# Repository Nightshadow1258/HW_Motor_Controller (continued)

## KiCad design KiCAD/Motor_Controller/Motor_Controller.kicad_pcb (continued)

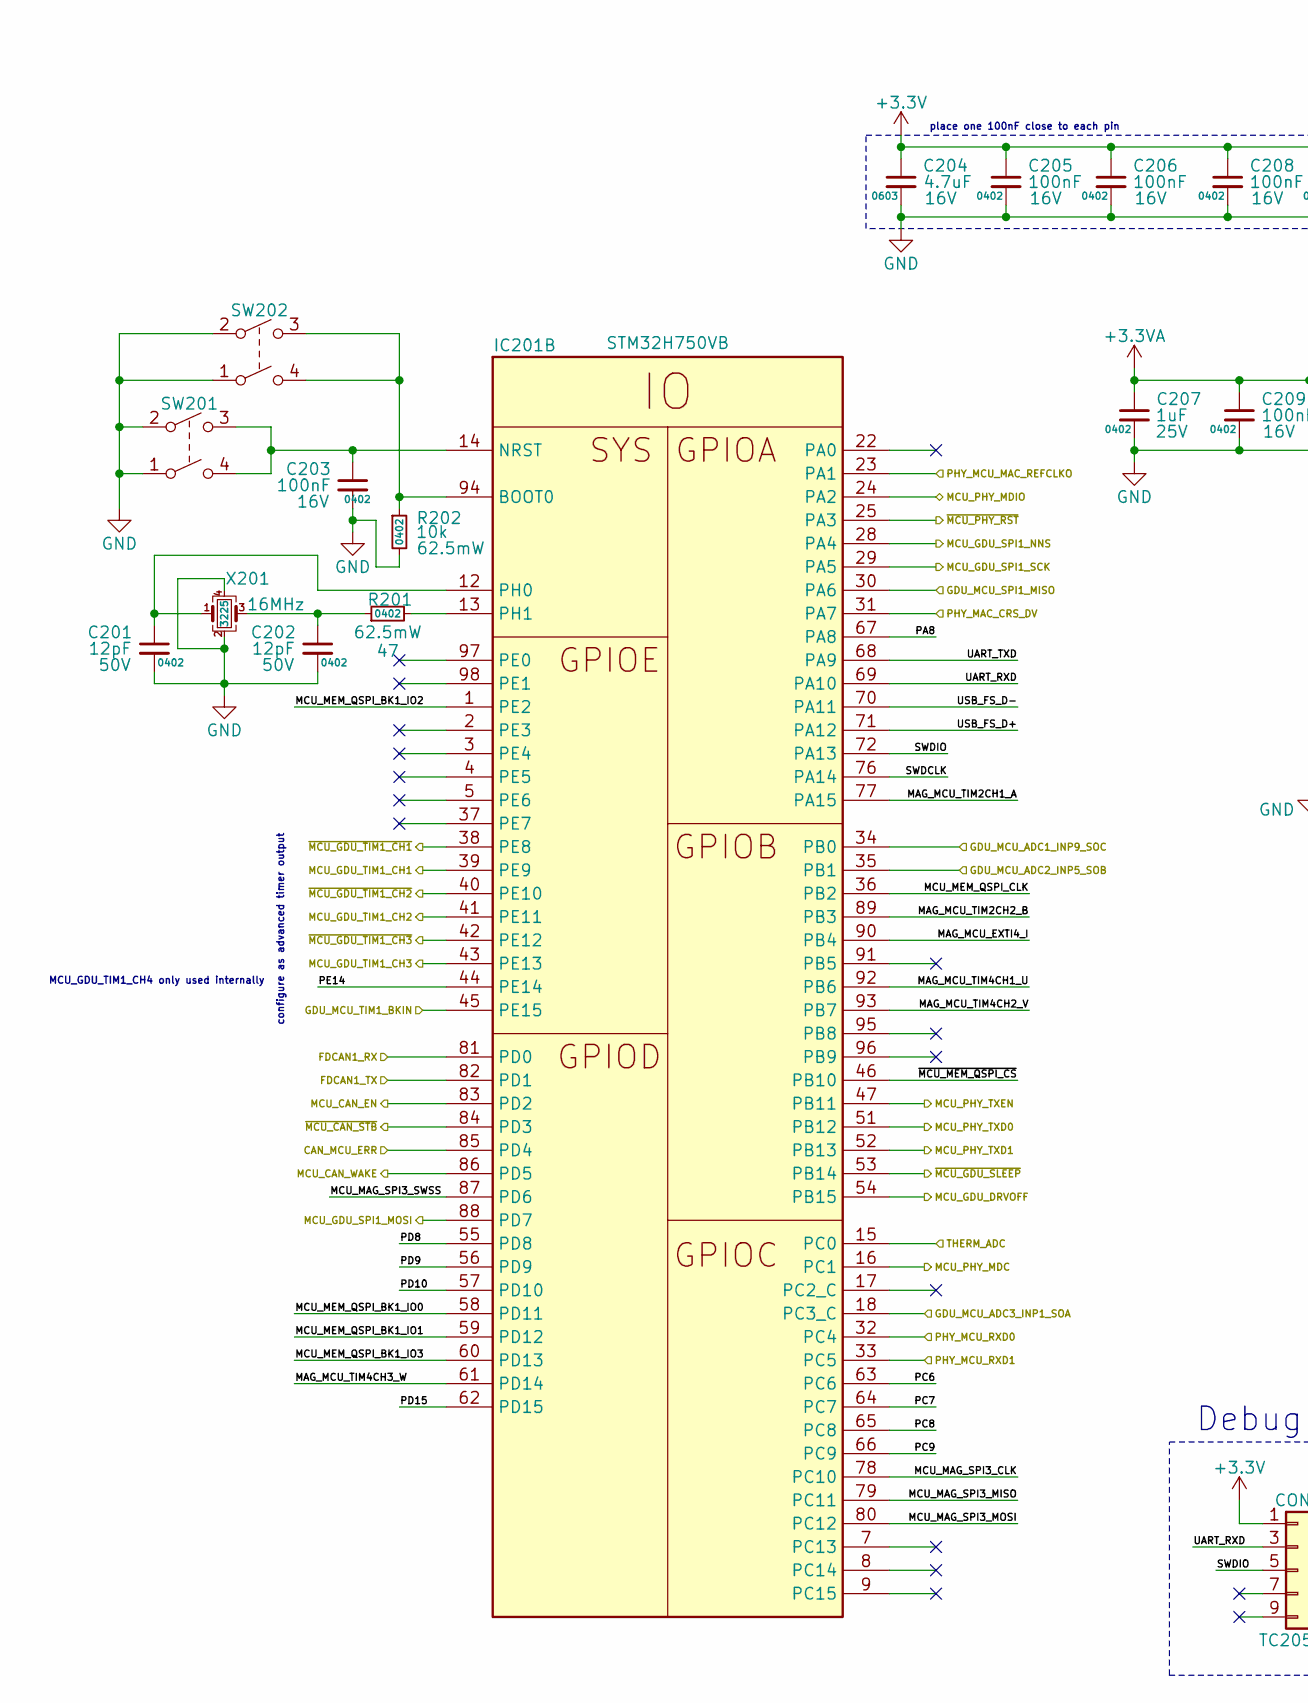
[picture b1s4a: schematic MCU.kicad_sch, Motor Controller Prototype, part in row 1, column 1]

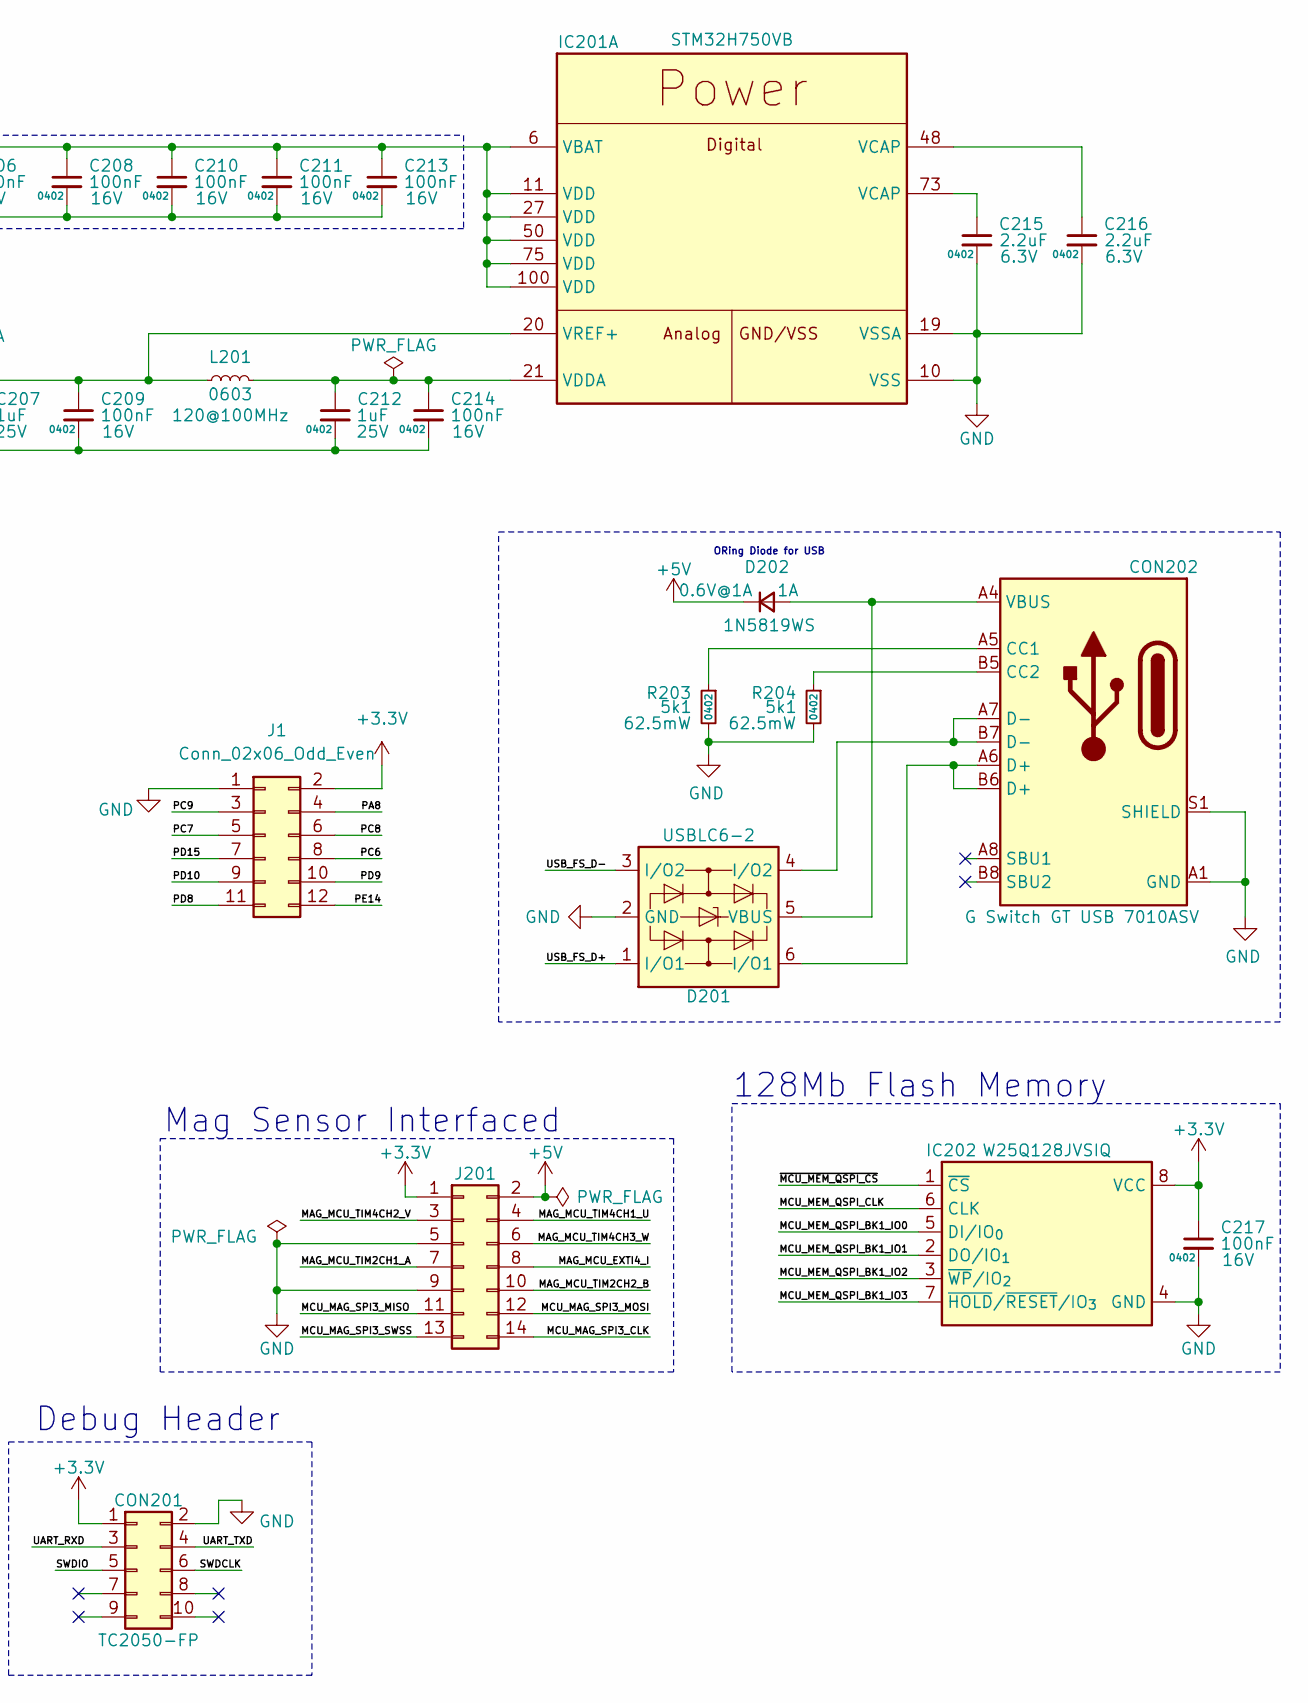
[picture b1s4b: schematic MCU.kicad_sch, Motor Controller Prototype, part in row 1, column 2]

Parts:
C201, C202: 12pF; C_0402_1005Metric; Voltage 50V; LCSC Part # C1547
C203, C205, C206, C208, C209, C210, C211, C213, C214, C217: 100nF; C_0402_1005Metric; Voltage 16V; LCSC Part # C1525
C204: 4.7uF; C_0603_1608Metric; Voltage 16V; LCSC Part # C19666
C207, C212: 1uF; C_0402_1005Metric; Voltage 25V; LCSC Part # C52923
C215, C216: 2.2uF; C_0402_1005Metric; Voltage 6.3V; LCSC Part # C12530
CON201: TC2050-FP; CON-TAG-CONNECT_TC2050-IDC
CON202: G Switch GT USB 7010ASV; CON-GEN-USB_C-16P; LCSC Part # C2988369
D201: USBLC6-2; SOT-23-6; LCSC Part # C7519
D202: 1N5819WS; D_SOD-323; LCSC Part # C191023
IC201: STM32H750VB; LQFP-100_14x14mm_P0.5mm; LCSC Part # C404010
IC202: W25Q128JVSIQ; SOIC-8_5.3x5.3mm_P1.27mm; LCSC Part # C97521
J1: Conn_02x06_Odd_Even; PinHeader_2x06_P2.54mm_Vertical
J201: Conn_02x07_Odd_Even; PinHeader_2x07_P2.54mm_Vertical
L201: FB-BLM18PG121SN1; L_0603_1608Metric; LCSC Part # C14709
R201: 47; R_0402_1005Metric; Power Rating 62.5mW; LCSC Part # C25118
R202: 10k; R_0402_1005Metric; Power Rating 62.5mW; LCSC Part # C25744
R203, R204: 5k1; R_0402_1005Metric; Power Rating 62.5mW; LCSC Part # C25905
SW201, SW202: SW-GEN-TS-1187A; SW-PUSH-DPST-XKS-TS-1187A; LCSC Part # C318884
X201: 16MHz; Crystal_SMD_3225-4Pin_3.2x2.5mm; LCSC Part # C12668

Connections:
+3.3V: C204.1, C205.1, C206.1, C208.1, C210.1, C211.1, C213.1, C217.1, CON201.1, IC201.6 (VBAT), IC201.11 (VDD), IC201.27 (VDD), IC201.50 (VDD), IC201.75 (VDD), IC201.100 (VDD), IC202.8 (VCC), J1.2, J201.1; also elsewhere on the board
+3.3VA: C207.1, C209.1, IC201.20 (VREF+), L201.1; also elsewhere on the board
+5V: D202.1 (K), J201.2; also elsewhere on the board
/Communication/CAN_MCU_ERR: IC201.85 (PD4); also elsewhere on the board
/Communication/CAN_MCU_RXD: IC201.81 (PD0); also elsewhere on the board
/Communication/MCU_CAN_EN: IC201.83 (PD2); also elsewhere on the board
/Communication/MCU_CAN_TXD: IC201.82 (PD1); also elsewhere on the board
/Communication/MCU_CAN_WAKE: IC201.86 (PD5); also elsewhere on the board
/Communication/MCU_PHY_MDC: IC201.16 (PC1); also elsewhere on the board
/Communication/MCU_PHY_MDIO: IC201.24 (PA2); also elsewhere on the board
/Communication/MCU_PHY_TXD0: IC201.51 (PB12); also elsewhere on the board
/Communication/MCU_PHY_TXD1: IC201.52 (PB13); also elsewhere on the board
/Communication/MCU_PHY_TXEN: IC201.47 (PB11); also elsewhere on the board
/Communication/PHY_MAC_CRS_DV: IC201.31 (PA7); also elsewhere on the board
/Communication/PHY_MCU_MAC_REFCLKO: IC201.23 (PA1); also elsewhere on the board
/Communication/PHY_MCU_RXD0: IC201.32 (PC4); also elsewhere on the board
/Communication/PHY_MCU_RXD1: IC201.33 (PC5); also elsewhere on the board
/Communication/~MCU_CAN_STB: IC201.84 (PD3); also elsewhere on the board
/Communication/~MCU_PHY_RST: IC201.25 (PA3); also elsewhere on the board
/MCU Board/GDU_MCU_ADC1_INP9_SOA: IC201.18 (PC3_C); also elsewhere on the board
/MCU Board/GDU_MCU_ADC2_INP5_SOB: IC201.35 (PB1); also elsewhere on the board
/MCU Board/GDU_MCU_ADC3_INP1_SOC: IC201.34 (PB0); also elsewhere on the board
/MCU Board/GDU_MCU_SPI1_MISO: IC201.30 (PA6); also elsewhere on the board
/MCU Board/GDU_MCU_TIM1_BKIN: IC201.45 (PE15); also elsewhere on the board
/MCU Board/MAG_MCU_EXTI4_I: IC201.90 (PB4), J201.8
/MCU Board/MAG_MCU_TIM2CH1_A: IC201.77 (PA15), J201.7
/MCU Board/MAG_MCU_TIM2CH2_B: IC201.89 (PB3), J201.10
/MCU Board/MAG_MCU_TIM4CH1_U: IC201.92 (PB6), J201.4
/MCU Board/MAG_MCU_TIM4CH2_V: IC201.93 (PB7), J201.3
/MCU Board/MAG_MCU_TIM4CH3_W: IC201.61 (PD14), J201.6
/MCU Board/MCU_GDU_DRVOFF: IC201.54 (PB15); also elsewhere on the board
/MCU Board/MCU_GDU_SPI1_MOSI: IC201.88 (PD7); also elsewhere on the board
/MCU Board/MCU_GDU_SPI1_NNS: IC201.28 (PA4); also elsewhere on the board
/MCU Board/MCU_GDU_SPI1_SCK: IC201.29 (PA5); also elsewhere on the board
/MCU Board/MCU_GDU_TIM1_CH1: IC201.39 (PE9); also elsewhere on the board
/MCU Board/MCU_GDU_TIM1_CH2: IC201.41 (PE11); also elsewhere on the board
/MCU Board/MCU_GDU_TIM1_CH3: IC201.43 (PE13); also elsewhere on the board
/MCU Board/MCU_MAG_SPI3_CLK: IC201.78 (PC10), J201.14
/MCU Board/MCU_MAG_SPI3_MISO: IC201.79 (PC11), J201.11
/MCU Board/MCU_MAG_SPI3_MOSI: IC201.80 (PC12), J201.12
/MCU Board/MCU_MAG_SPI3_SWSS: IC201.87 (PD6), J201.13
/MCU Board/MCU_MEM_QSPI_BK1_IO0: IC201.58 (PD11), IC202.5 (DI/IO_{0})
/MCU Board/MCU_MEM_QSPI_BK1_IO1: IC201.59 (PD12), IC202.2 (DO/IO_{1})
/MCU Board/MCU_MEM_QSPI_BK1_IO2: IC201.1 (PE2), IC202.3 (~WP/IO_{2})
/MCU Board/MCU_MEM_QSPI_BK1_IO3: IC201.60 (PD13), IC202.7 (~HOLD/~RESET/IO_{3})
/MCU Board/MCU_MEM_QSPI_CLK: IC201.36 (PB2), IC202.6 (CLK)
/MCU Board/PA8: IC201.67 (PA8), J1.4
/MCU Board/PC6: IC201.63 (PC6), J1.8
/MCU Board/PC7: IC201.64 (PC7), J1.5
/MCU Board/PC8: IC201.65 (PC8), J1.6
/MCU Board/PC9: IC201.66 (PC9), J1.3
/MCU Board/PD8: IC201.55 (PD8), J1.11
/MCU Board/PD9: IC201.56 (PD9), J1.10
/MCU Board/PD10: IC201.57 (PD10), J1.9
/MCU Board/PD15: IC201.62 (PD15), J1.7
/MCU Board/PE14: IC201.44 (PE14), J1.12
/MCU Board/SWDCLK: CON201.6, IC201.76 (PA14)
/MCU Board/SWDIO: CON201.5, IC201.72 (PA13)
/MCU Board/THERM_ADC: IC201.15 (PC0); also elsewhere on the board
/MCU Board/UART_RXD: CON201.3, IC201.69 (PA10)
/MCU Board/UART_TXD: CON201.4, IC201.68 (PA9)
/MCU Board/USB_FS_D+: D201.1 (I/O1), IC201.71 (PA12)
/MCU Board/USB_FS_D-: D201.3 (I/O2), IC201.70 (PA11)
/MCU Board/~MCU_GDU_SLEEP: IC201.53 (PB14); also elsewhere on the board
/MCU Board/~MCU_GDU_TIM1_CH1: IC201.38 (PE8); also elsewhere on the board
/MCU Board/~MCU_GDU_TIM1_CH2: IC201.40 (PE10); also elsewhere on the board
/MCU Board/~MCU_GDU_TIM1_CH3: IC201.42 (PE12); also elsewhere on the board
/MCU Board/~MCU_MEM_QSPI_CS: IC201.46 (PB10), IC202.1 (~CS)
GND: C201.2, C202.2, C203.2, C204.2, C205.2, C206.2, C207.2, C208.2, C209.2, C210.2, C211.2, C212.2, C213.2, C214.2, C215.2, C216.2, C217.2, CON201.2, CON202.A1 (GND), CON202.A12 (GND), CON202.B1 (GND), CON202.B12 (GND), CON202.S1 (SHIELD), D201.2 (GND), IC201.10 (VSS), IC201.19 (VSSA), IC201.26 (VSS), IC201.49 (VSS), IC201.74 (VSS), IC201.99 (VSS), IC202.4 (GND), J1.1, J201.5, J201.9, R202.2, R203.2, R204.2, SW201.1, SW201.2 (3), SW202.1, SW202.2 (3), X201.2, X201.4; also elsewhere on the board
unnamed: C202.1, R201.1, X201.3
unnamed: C215.1, IC201.73 (VCAP)
unnamed: C216.1, IC201.48 (VCAP)
unnamed: CON202.A5 (CC1), R203.1
unnamed: CON202.B5 (CC2), R204.1
unnamed: CON202.A6 (D+), CON202.B6 (D+), D201.6 (I/O1)
unnamed: CON202.A7 (D-), CON202.B7 (D-), D201.4 (I/O2)
unnamed: CON202.A4 (VBUS), CON202.A9 (VBUS), CON202.B4 (VBUS), CON202.B9 (VBUS), D201.5 (VBUS), D202.2 (A)
unnamed: C212.1, C214.1, IC201.21 (VDDA), L201.2
unnamed: IC201.94 (BOOT0), R202.1, SW202.3 (4), SW202.4
unnamed: C203.1, IC201.14 (NRST), SW201.3 (4), SW201.4
unnamed: C201.1, IC201.12 (PH0), X201.1
unnamed: IC201.13 (PH1), R201.2

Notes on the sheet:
Mag Sensor Interfaced
ORing Diode for USB
128Mb Flash Memory
MCU_GDU_TIM1_CH4 only used internally
Debug Header
configure as advanced timer output
place one 100nF close to each pin

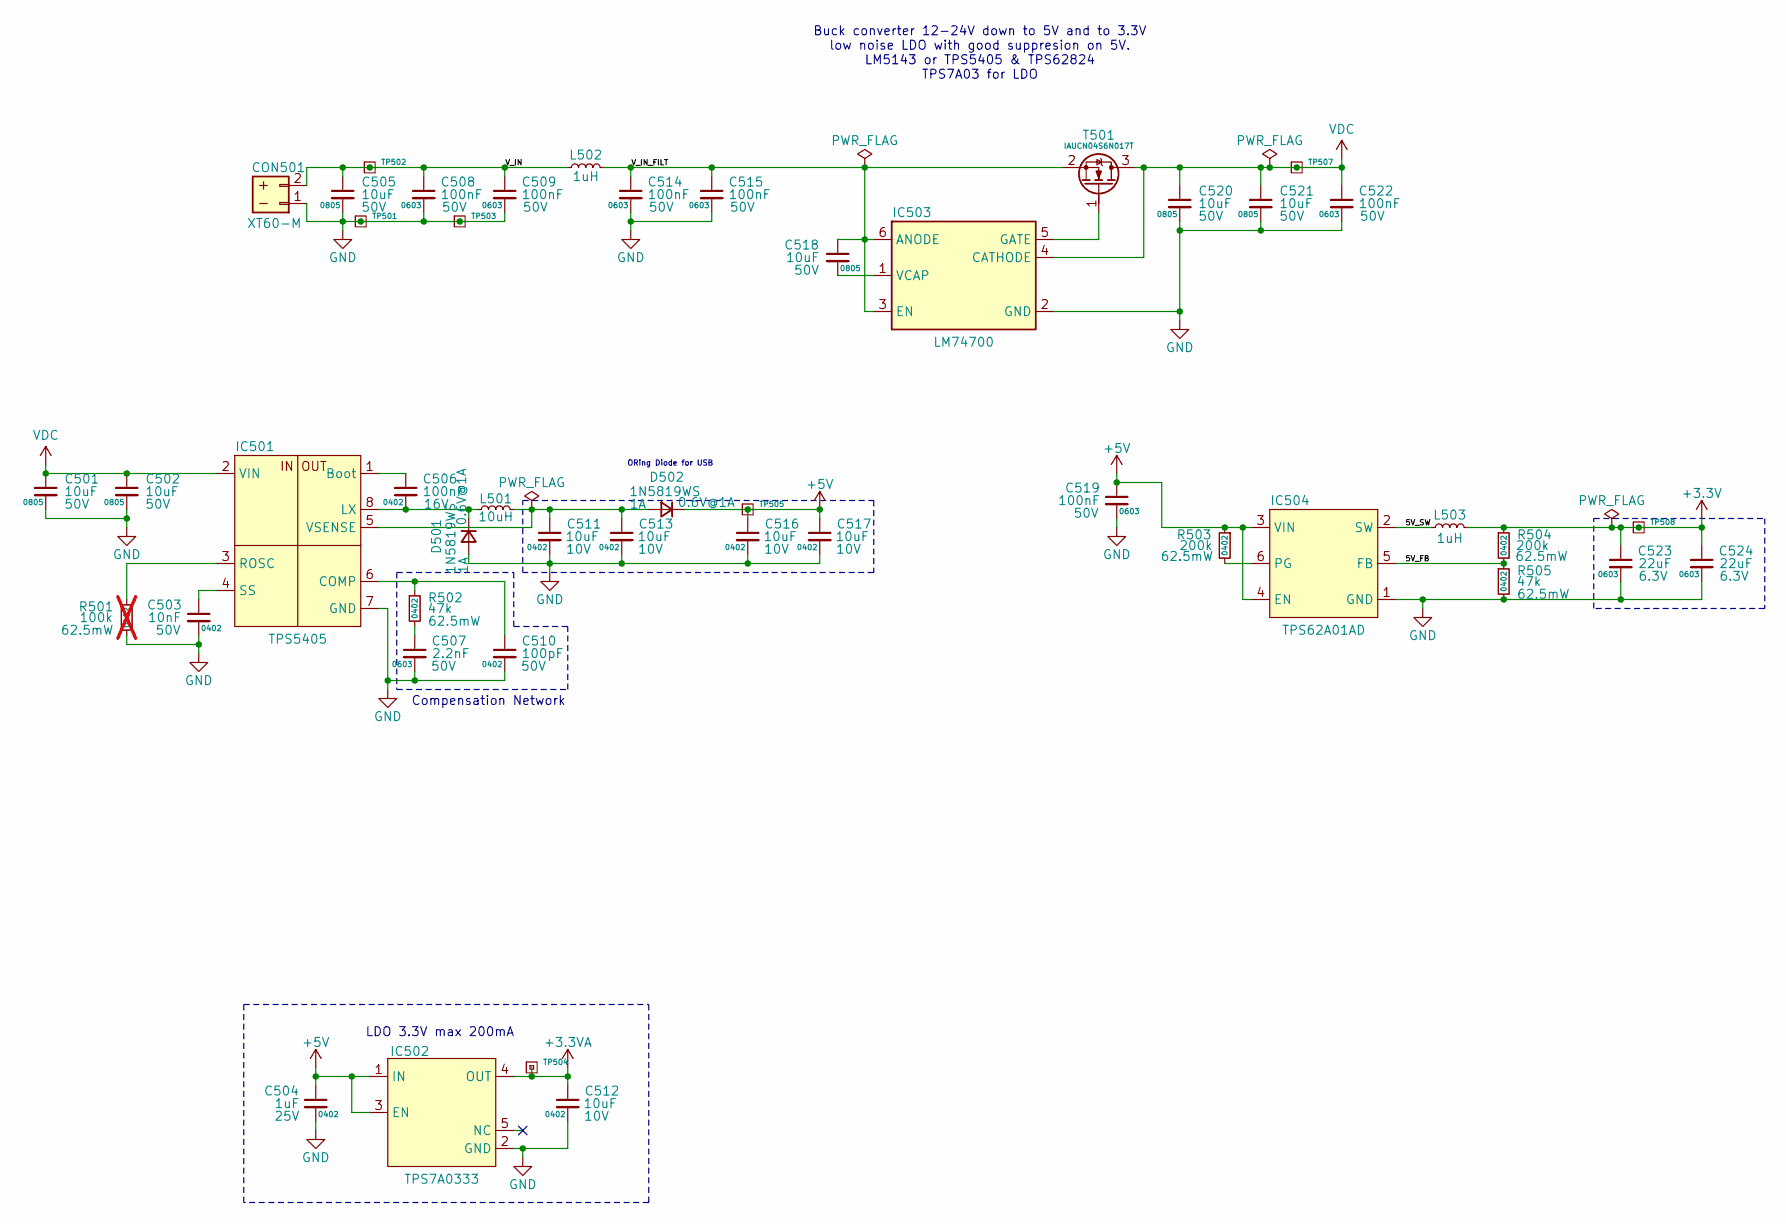
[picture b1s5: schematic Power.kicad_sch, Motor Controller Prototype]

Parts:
C501, C502, C505, C518, C520, C521: 10uF; C_0805_2012Metric; Voltage 50V; LCSC Part # C440198
C503: 10nF; C_0402_1005Metric; Voltage 50V; LCSC Part # C15195
C504: 1uF; C_0402_1005Metric; Voltage 25V; LCSC Part # C52923
C506: 100nF; C_0402_1005Metric; Voltage 16V; LCSC Part # C1525
C507: 2.2nF; C_0603_1608Metric; Voltage 50V; LCSC Part # C1604
C508, C509, C514, C515, C519, C522: 100nF; C_0603_1608Metric; Voltage 50V; LCSC Part # C14663
C510: 100pF; C_0402_1005Metric; Voltage 50V; LCSC Part # C1546
C511, C512, C513, C516, C517: 10uF; C_0603_1608Metric; Voltage 10V; LCSC Part # C96446
C523, C524: 22uF; C_0805_2012Metric; Voltage 6.3V; LCSC Part # C59461
CON501: XT60-M; AMASS_XT60-M_1x02_P7.20mm_Vertical
D501, D502: 1N5819WS; D_SOD-323; LCSC Part # C191023
IC501: TPS5405; SOIC-8_3.9x4.9mm_P1.27mm; LCSC Part # C488409
IC502: TPS7A0333; SOT-23-5; LCSC Part # C2873330
IC503: LM74700; SOT-23-6; LCSC Part # C2941042
IC504: TPS62A01AD; SOT-563; LCSC Part # C5181455
L501: 10uH; L_SXN_SMNR4020; LCSC Part # C135263
L502: 1uH; L_Coilcraft_XAL7030-102; LCSC Part # C19191626
L503: 1uH; L_1008_2520Metric; LCSC Part # C435392
R501: 100k; R_0402_1005Metric; Power Rating 62.5mW; LCSC Part # C25741; not fitted
R502, R505: 47k; R_0402_1005Metric; Power Rating 62.5mW; LCSC Part # C25792
R503, R504: 200k; R_0402_1005Metric; Power Rating 62.5mW; LCSC Part # C25764
T501: IAUCN04S6N017T; T-MOSN-LHDSO-10-1
TP501, TP502, TP503, TP504, TP505, TP507, TP508: Testpoint-BASE; TP_THT_D0.8mm

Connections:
+3.3V: C523.1, C524.1, L503.2, R504.1, TP508.1; also elsewhere on the board
+3.3VA: C512.1, IC502.4 (OUT), TP504.1; also elsewhere on the board
+5V: C504.1, C516.1, C517.1, C519.1, D502.1 (K), IC502.1 (IN), IC502.3 (EN), IC504.3 (VIN), IC504.4 (EN), R503.1, TP505.1; also elsewhere on the board
/Power/5V_FB: IC504.5 (FB), R504.2, R505.1
/Power/5V_SW: IC504.2 (SW), L503.1
/Power/V_IN: C505.1, C508.1, C509.1, CON501.2 (+), L502.1, TP502.1
/Power/V_IN_FILT: C514.1, C515.1, C518.1, IC503.3 (EN), IC503.6 (ANODE), L502.2, T501.2 (S)
GND: C501.2, C502.2, C503.2, C504.2, C505.2, C507.2, C508.2, C509.2, C510.2, C511.2, C512.2, C513.2, C514.2, C515.2, C516.2, C517.2, C519.2, C520.2, C521.2, C522.2, C523.2, C524.2, CON501.1 (-), D501.2 (A), IC501.7 (GND), IC502.2 (GND), IC503.2 (GND), IC504.1 (GND), R501.2, R505.2, TP501.1, TP503.1; also elsewhere on the board
unnamed: C507.1, R502.2
unnamed: C506.2, D501.1 (K), IC501.8 (LX), L501.1
unnamed: C511.1, C513.1, D502.2 (A), IC501.5 (VSENSE), L501.2
unnamed: C506.1, IC501.1 (Boot)
unnamed: C510.1, IC501.6 (COMP), R502.1
unnamed: IC501.3 (ROSC), R501.1
unnamed: C503.1, IC501.4 (SS)
unnamed: IC503.5 (GATE), T501.1 (G)
unnamed: C518.2, IC503.1 (VCAP)
unnamed: IC504.6 (PG), R503.2
VDC: C501.1, C502.1, C520.1, C521.1, C522.1, IC501.2 (VIN), IC503.4 (CATHODE), T501.3 (D), TP507.1; also elsewhere on the board

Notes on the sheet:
LDO 3.3V max 200mA
ORing Diode for USB
Buck converter 12-24V down to 5V and to 3.3V low noise LDO with good suppresion on 5V. LM5143 or TPS5405 & TPS62824 TPS7A03 for LDO
Compensation Network

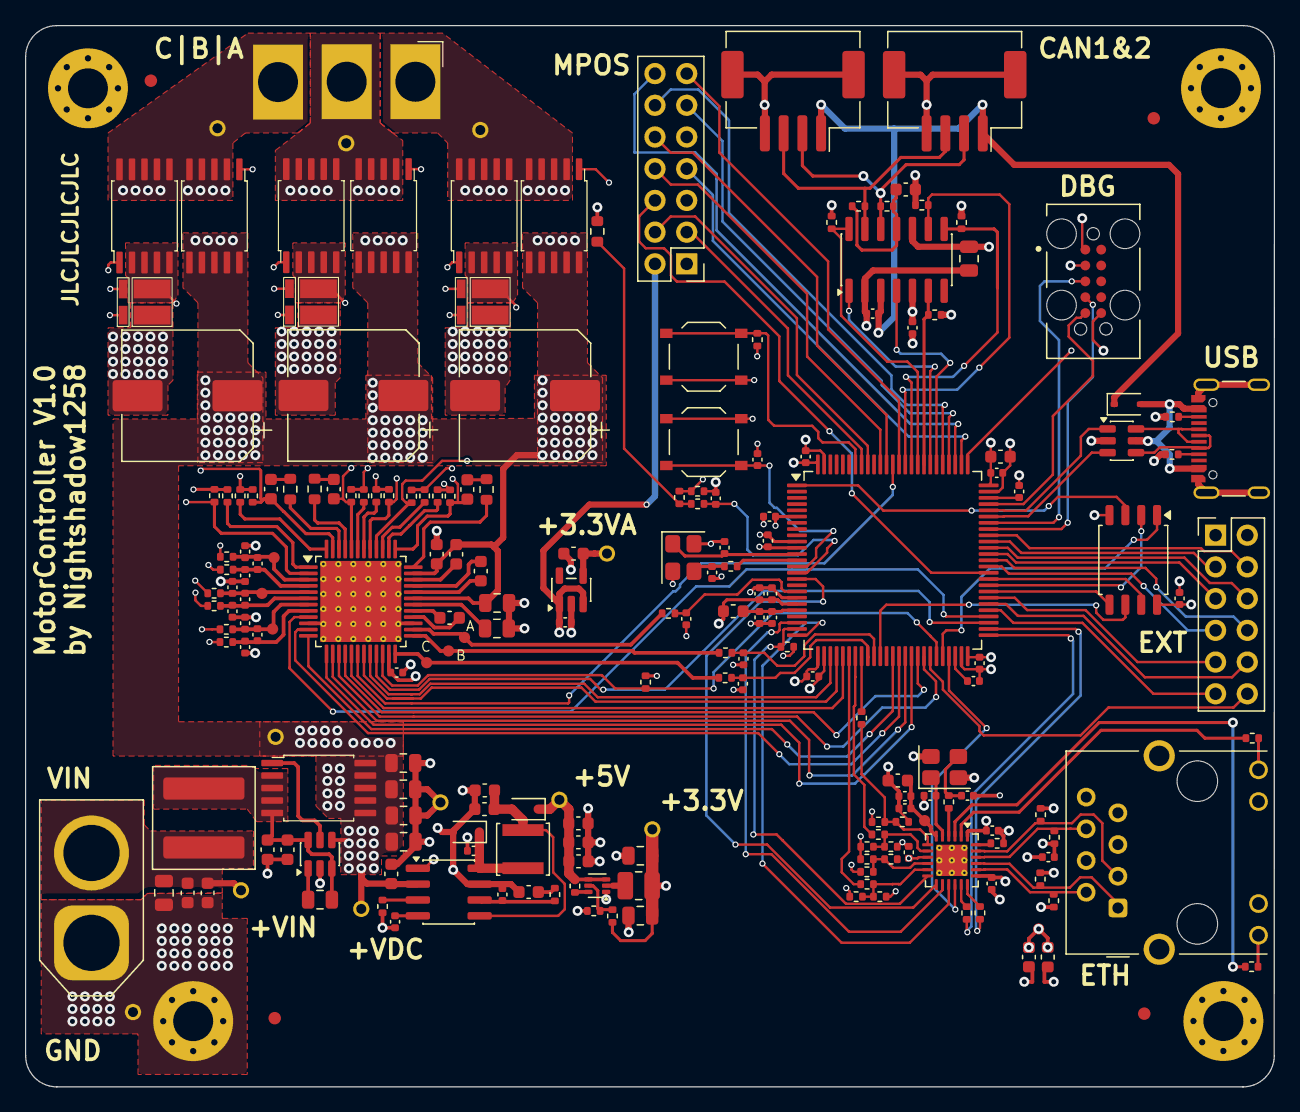
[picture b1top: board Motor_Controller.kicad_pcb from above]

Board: 4 copper layers, 100.0 x 85.0 mm, 216 parts (0 on the bottom side), 166 nets.

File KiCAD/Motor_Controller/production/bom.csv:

Designator,Footprint,Quantity,Value,LCSC Part #
"C201, C202, C410, C412",0402,4,12pF,C1547
"C203, C205, C206, C208, C209, C210, C211, C213, C214, C217, C301, C403, C406, C408, C409, C411, C414, C506",0402,18,100nF,C1525
"C204, C405, C413",0603,3,4.7uF,C19666
"C207, C212, C326, C402, C504",0402,5,1uF,C52923
"C215, C216",0402,2,2.2uF,C12530
"C302, C303, C407, C501, C502, C505, C518, C520, C521",0805,9,10uF,C440198
"C304, C305, C306, C404",0402,4,470pF,C1537
"C307, C308, C315, C316, C319, C321, C325",0603,7,1uF,C15849
"C309, C310, C311, C312, C313, C314, C317, C318, C320",0402,9,1nF,C1523
"C322, C323, C324",CP_Elec_10x10,3,220uF,C79124
C503,0402,1,10nF,C15195
C507,0603,1,2.2nF,C1604
"C508, C509, C514, C515, C519, C522",0603,6,100nF,C14663
C510,0402,1,100pF,C1546
"C511, C512, C513, C516, C517",0603,5,10uF,C96446
"C523, C524",0805,2,22uF,C59461
CON201,CON-TAG-CONNECT_TC2050-IDC,1,TC2050-FP,
CON202,CON-GEN-USB_C-16P,1,G Switch GT USB 7010ASV,C2988369
CON401,CON-RJ45-HR911105A-H,1,CON-RJ45-HR913550A,C163507
"CON402, CON403",CON-SM04B-ZESS-TB,2,SM04B-ZESS-TB,
CON501,AMASS_XT60-M_1x02_P7.20mm_Vertical,1,XT60-M,
D201,SOT-23-6,1,USBLC6-2,C7519
"D202, D501, D502",D_SOD-323,3,1N5819WS,C191023
"FID101, FID102, FID103, FID104",PCB-FID-JLCPCB,4,Fiducal-JLCPPCB,
IC201,LQFP-100_14x14mm_P0.5mm,1,STM32H750VB,C2969869
IC202,SOIC-8_5.3x5.3mm_P1.27mm,1,W25Q128JVSIQ,
IC301,Texas_PHP0048E_HTQFP-48-1EP_7x7mm_P0.5mm_EP6.5x6.5mm_Mask3.62x3.62mm_ThermalVias,1,DRV8334,
IC401,SOIC-14_3.9x8.7mm_P1.27mm,1,IC-LOGIC-TJA1043T,C140826
IC501,SOIC-8_3.9x4.9mm_P1.27mm,1,TPS5405,C488409
IC502,SOT-23-5,1,TPS7A0333,C2873330
IC503,SOT-23-6,1,LM74700,C2941042
IC504,SOT-563,1,TPS62A01AD,C5181455
J1,PinHeader_2x06_P2.54mm_Vertical,1,Conn_02x06_Odd_Even,
J201,PinHeader_2x07_P2.54mm_Vertical,1,Conn_02x07_Odd_Even,
J301,CON-01x03-10-AWG,1,Conn_01x03,
"L201, L401",0603,2,FB-BLM18PG121SN1,C14709
L501,L_SXN_SMNR4020,1,10uH,    C135263
L502,L_Coilcraft_XAL7030-102,1,1uH,C19191626
L503,1008,1,1uH,C435392
"MH101, MH102, MH103, MH104",MountingHole_3.2mm_M3_Pad_Via,4,~,
"R201, R412",0402,2,47,C25118
"R202, R301, R330, R401, R402, R403, R407",0402,7,10k,C25744
"R203, R204",0402,2,5k1,C25905
"R302, R303, R304, R310, R313, R318, R319, R324, R325, R332",0402,10,0,C17168
"R305, R306, R307, R308, R311, R312",0402,6,10,C25077
"R309, R317, R323",0603,3,4.7,C23164
"R314, R315, R320, R321, R326, R327, R501",0402,7,100k,C25741
"R316, R322, R328",R-SH-1216_flip,3,1m,
R329,0603,1,10k,C142556
"R331, R503, R504",0402,3,200k,C25764
"R404, R405, R406, R409, R410, R411",0402,6,100,C25076
R408,0402,1,2k,C4109
"R413, R414",0402,2,60.4,C60310
R415,0402,1,12.1k,C25852
"R416, R418",0402,2,330,C25104
"R417, R419, R420, R421",0402,4,49.9,C25120
"R422, R424, R426, R428, R429",0402,5,4k7,C25900
"R502, R505",0402,2,47k,C25792
"SW201, SW202",SW-PUSH-DPST-XKS-TS-1187A,2,SW-GEN-TS-1187A,C318884
"T301, T302, T303, T304, T305, T306, T501",T-MOSN-LHDSO-10-1,7,IAUCN04S6N017T,
"TP301, TP308, TP309, TP310, TP501, TP502, TP503, TP504, TP505, TP507, TP508",TP_THT_D0.8mm,11,Testpoint-BASE,
"TP302, TP303, TP304, TP305, TP306, TP307, TP401, TP402",TP_Pad_D0.9mm,8,TP,
U401,VQFN-24-1EP_4x4mm_P0.5mm_EP2.5x2.5mm_ThermalVias,1,IC-LOGIC-LAN8720A,C621425
X201,Crystal_SMD_3225-4Pin_3.2x2.5mm,1,16MHz,C12668
X401,Crystal_SMD_3225-4Pin_3.2x2.5mm,1,25MHz,C9006

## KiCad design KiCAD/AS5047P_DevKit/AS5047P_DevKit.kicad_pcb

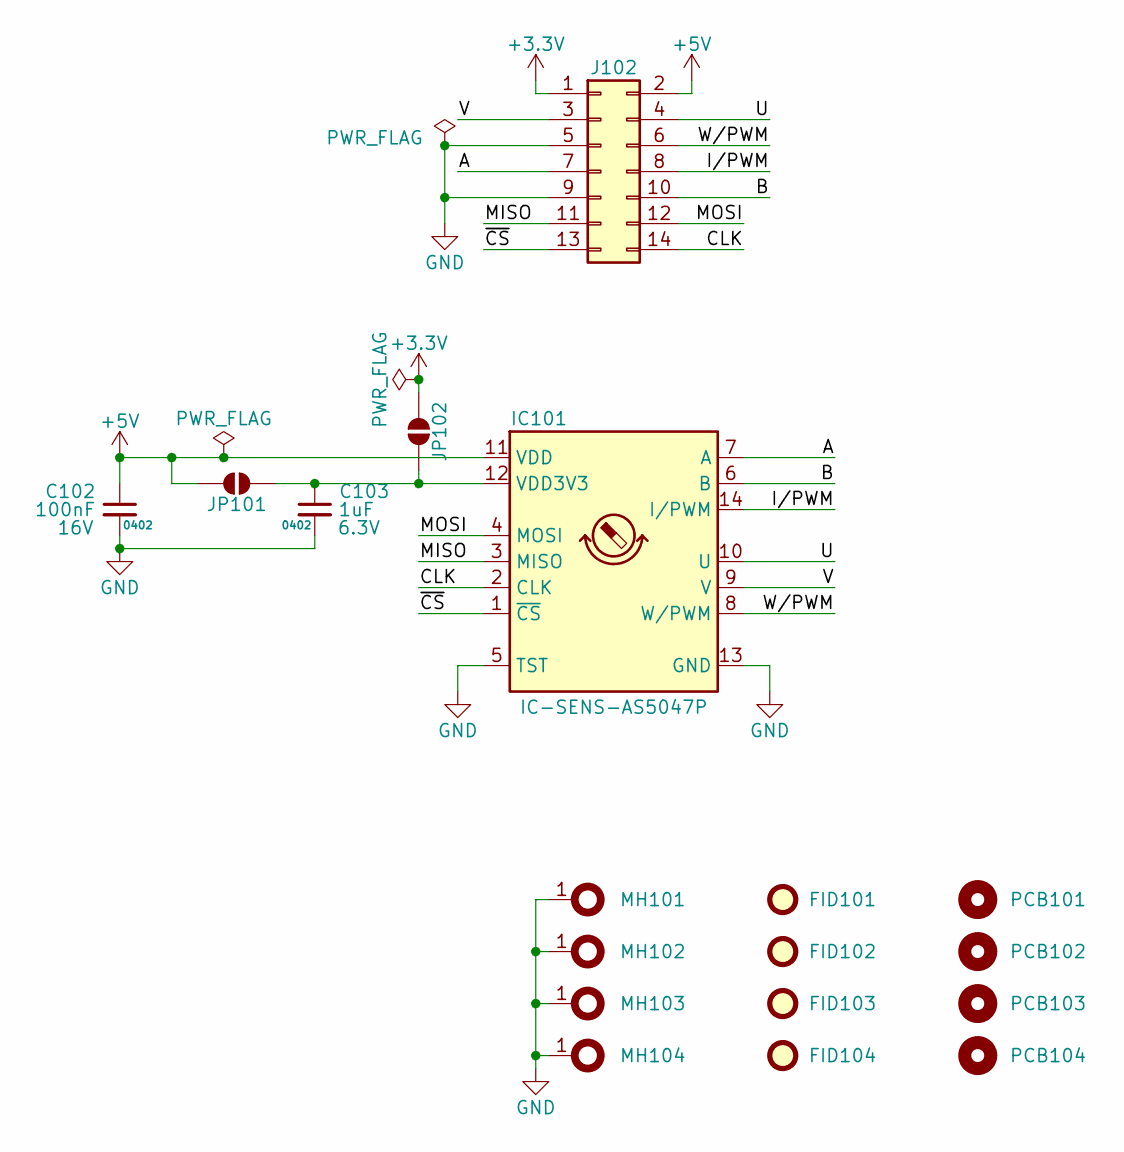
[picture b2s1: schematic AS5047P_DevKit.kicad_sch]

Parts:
C102: 100nF; C_0402_1005Metric; Voltage 16V; LCSC Part # C1525
C103: 1uF; C_0402_1005Metric; Voltage 6.3V; LCSC Part # C15525
FID101, FID102, FID103, FID104: Fiducal-JLCPPCB; PCB-FID-JLCPCB
IC101: IC-SENS-AS5047P; TSSOP-14_4.4x5mm_P0.65mm; LCSC Part # C962063
J102: Conn_02x07_Odd_Even; PinHeader_2x07_P2.54mm_Vertical
JP101, JP102: SolderJumper_2_Open; SolderJumper-2_P1.3mm_Open_RoundedPad1.0x1.5mm
MH101, MH102, MH103, MH104: MountingHole_2.5mm_Pad_Via
PCB101, PCB102, PCB103, PCB104: Tooling Hole JLCPCB; PCB-NPTH-JLCPCB

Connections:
+3.3V: J102.1, JP102.1 (A)
+5V: C102.1, IC101.11 (VDD), J102.2, JP101.2 (B)
/A: IC101.7 (A), J102.7
/B: IC101.6 (B), J102.10
/CLK: IC101.2 (CLK), J102.14
/I/PWM: IC101.14 (I/PWM), J102.8
/MISO: IC101.3 (MISO), J102.11
/MOSI: IC101.4 (MOSI), J102.12
/U: IC101.10 (U), J102.4
/V: IC101.9 (V), J102.3
/W/PWM: IC101.8 (W/PWM), J102.6
/~CS: IC101.1 (~CS), J102.13
GND: C102.2, C103.2, IC101.5 (TST), IC101.13 (GND), J102.5, J102.9, MH101.1, MH102.1, MH103.1, MH104.1
unnamed: C103.1, IC101.12 (VDD3V3), JP101.1 (A), JP102.2 (B)

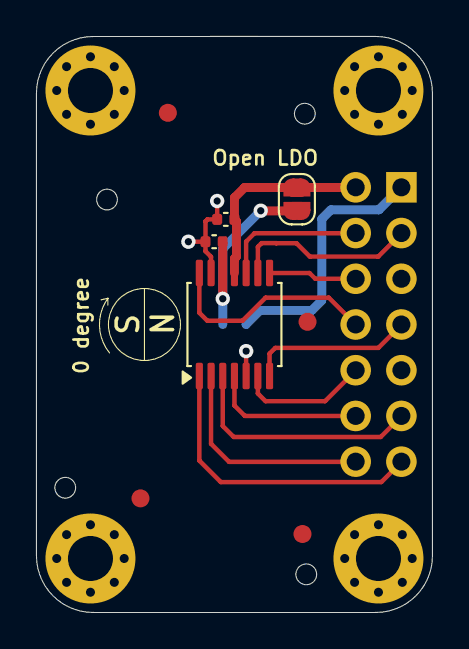
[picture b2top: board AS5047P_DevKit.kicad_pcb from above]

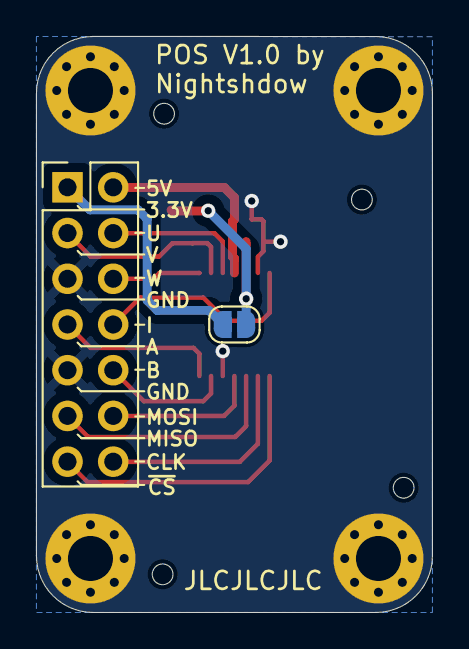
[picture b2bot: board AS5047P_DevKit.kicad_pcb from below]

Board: 2 copper layers, 22.0 x 32.0 mm, 18 parts (2 on the bottom side), 14 nets.

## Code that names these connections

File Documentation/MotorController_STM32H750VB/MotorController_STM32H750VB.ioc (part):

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Mcu.Name=STM32H750VBTx
Mcu.Package=LQFP100
Mcu.UserName=STM32H750VBTx
PA1.Mode=RMII
PA1.Signal=ETH_REF_CLK
PA10.Mode=Asynchronous
PA10.Signal=USART1_RX
PA11.Mode=Device_Only
PA11.Signal=USB_OTG_FS_DM
PA12.Mode=Device_Only
PA12.Signal=USB_OTG_FS_DP
PA13\ (JTMS/SWDIO).Mode=Serial_Wire
PA13\ (JTMS/SWDIO).Signal=DEBUG_JTMS-SWDIO
PA14\ (JTCK/SWCLK).Mode=Serial_Wire
PA14\ (JTCK/SWCLK).Signal=DEBUG_JTCK-SWCLK
PA15\ (JTDI).Signal=S_TIM2_CH1_ETR
PA2.Mode=RMII
PA2.Signal=ETH_MDIO
PA3.GPIOParameters=GPIO_Label
PA3.GPIO_Label=PHY_RST
PA3.Signal=GPIO_Output
PA4.Mode=NSS_Signal_Hard_Output
PA4.Signal=SPI1_NSS
PA5.Mode=Full_Duplex_Master
PA5.Signal=SPI1_SCK
PA6.Mode=Full_Duplex_Master
PA6.Signal=SPI1_MISO
PA7.Mode=RMII
PA7.Signal=ETH_CRS_DV
PA9.Mode=Asynchronous
PA9.Signal=USART1_TX
PB0.Signal=ADCx_INP9
PB1.Signal=ADCx_INP5
PB10.Mode=Single Bank 1
PB10.Signal=QUADSPI_BK1_NCS
PB11.Mode=RMII
PB11.Signal=ETH_TX_EN
PB12.Mode=RMII
PB12.Signal=ETH_TXD0
PB13.Mode=RMII
PB13.Signal=ETH_TXD1
PB2.Mode=Single Bank 1
PB2.Signal=QUADSPI_CLK
PB3\ (JTDO/TRACESWO).Signal=S_TIM2_CH2
PB4\ (NJTRST).GPIOParameters=GPIO_Label
PB4\ (NJTRST).GPIO_Label=EXTI_ABI
PB4\ (NJTRST).Signal=GPXTI4
PB6.Signal=S_TIM4_CH1
PB7.Signal=S_TIM4_CH2
PC0.Signal=ADCx_INP10
PC1.Mode=RMII
PC1.Signal=ETH_MDC
PC10.Mode=Full_Duplex_Master
PC10.Signal=SPI3_SCK
PC11.Mode=Full_Duplex_Master
PC11.Signal=SPI3_MISO
PC12.Mode=Full_Duplex_Master
PC12.Signal=SPI3_MOSI
PC3_C.Mode=IN1-Single-Ended
PC3_C.Signal=ADC3_INP1
PC4.Mode=RMII
PC4.Signal=ETH_RXD0
PC5.Mode=RMII
PC5.Signal=ETH_RXD1
PD0.Mode=FDCAN_Activate
PD0.Signal=FDCAN1_RX
PD1.Mode=FDCAN_Activate
PD1.Signal=FDCAN1_TX
PD11.Mode=Single Bank 1
PD11.Signal=QUADSPI_BK1_IO0
PD12.Mode=Single Bank 1
PD12.Signal=QUADSPI_BK1_IO1
PD13.Mode=Single Bank 1
PD13.Signal=QUADSPI_BK1_IO3
PD14.Signal=S_TIM4_CH3
PD2.GPIOParameters=GPIO_Label
PD2.GPIO_Label=CAN_EN
PD2.Signal=GPIO_Output
PD3.GPIOParameters=GPIO_Label
PD3.GPIO_Label=CAN_NSTB
PD3.Signal=GPIO_Output
PD4.GPIOParameters=GPIO_Label
PD4.GPIO_Label=CAN_ERR
PD4.Signal=GPIO_Input
PD5.Signal=GPIO_Output
PD6.GPIOParameters=GPIO_Label
PD6.GPIO_Label=SPI3_SWSS
PD6.Signal=GPIO_Output
PD7.Mode=Full_Duplex_Master
PD7.Signal=SPI1_MOSI
PD8.Signal=GPXTI8
PE10.Signal=TIM1_CH2N
PE11.Signal=S_TIM1_CH2
PE12.Signal=TIM1_CH3N
PE13.Signal=S_TIM1_CH3
PE14.Signal=S_TIM1_CH4
PE15.Mode=Activate-Break-Input
PE15.Signal=TIM1_BKIN
PE2.Mode=Single Bank 1
PE2.Signal=QUADSPI_BK1_IO2
PE6.Mode=Activate-Break-Input-2
PE6.Signal=TIM1_BKIN2
PE8.Signal=TIM1_CH1N
PE9.Signal=S_TIM1_CH1
PH0-OSC_IN\ (PH0).Mode=HSE-External-Oscillator
PH0-OSC_IN\ (PH0).Signal=RCC_OSC_IN
PH1-OSC_OUT\ (PH1).Mode=HSE-External-Oscillator
PH1-OSC_OUT\ (PH1).Signal=RCC_OSC_OUT
RCC.HSE_VALUE=16000000
RCC.SYSCLKFreq_VALUE=480000000
RCC.SYSCLKSource=RCC_SYSCLKSOURCE_PLLCLK
board=custom

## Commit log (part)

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2026-01-08 initial commit. SCH first draft done & started with Layout.
2026-01-09 Continued with the component placement. Still work to do
2026-01-10 changed low side shunt from 0.3mOhm to 1mOhm type and smaller footrprint. Updated rough component placement. Changed 10uH Coil of 5V regulator to smaller footprint due to lower expected current draw 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
2026-01-12 layout CAN Interface down.
2026-01-12 layout USB Interface down.
2026-01-15 GDU base routing done. Added SCH pdf for MPS.¨
2026-02-04 Prototype Design finished and ordered.
